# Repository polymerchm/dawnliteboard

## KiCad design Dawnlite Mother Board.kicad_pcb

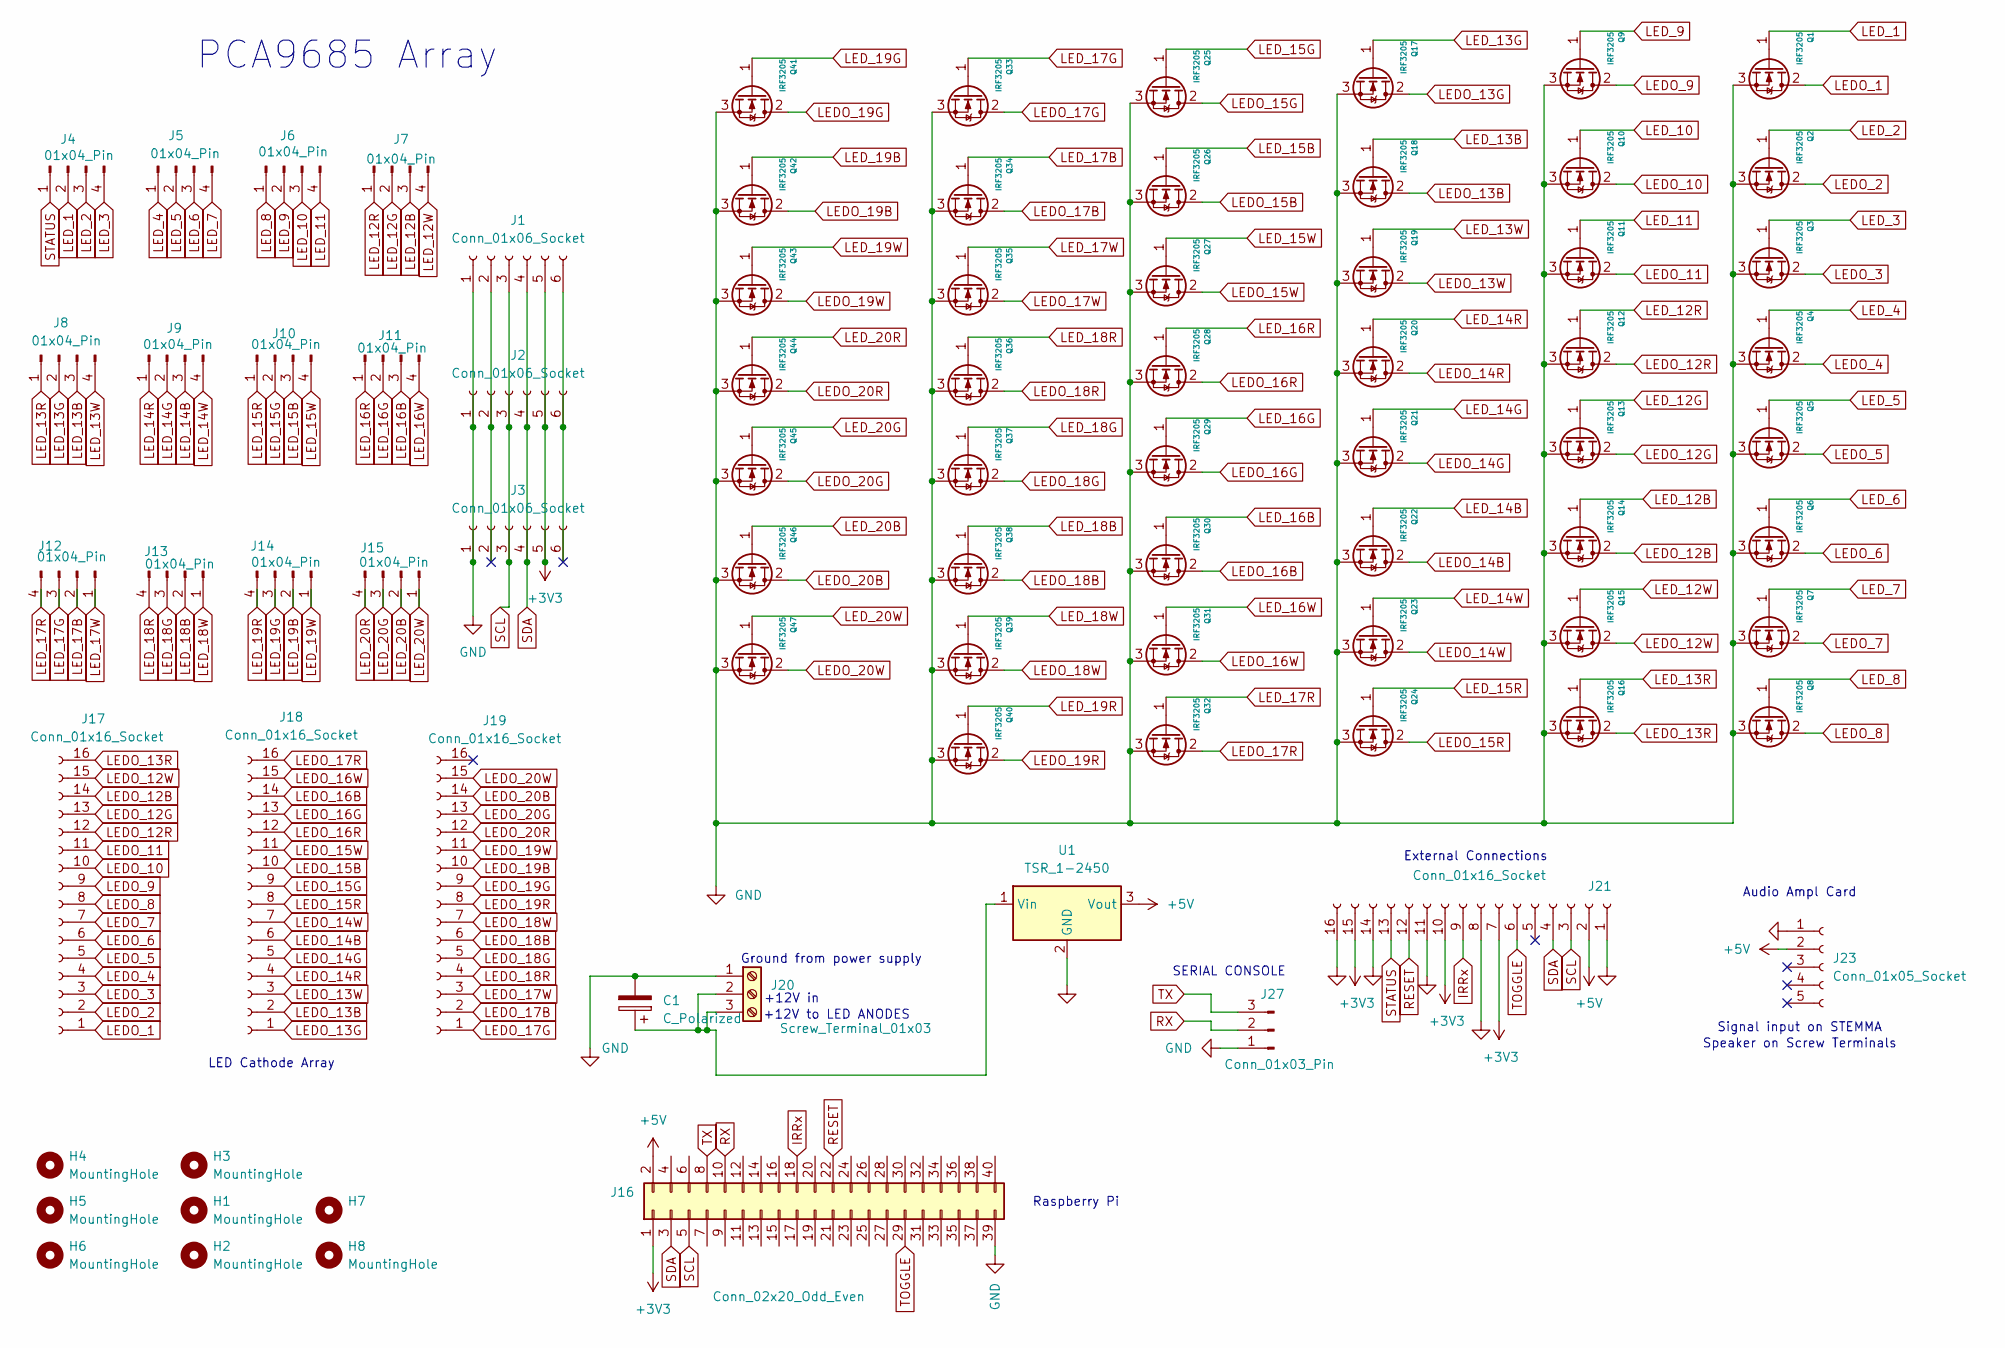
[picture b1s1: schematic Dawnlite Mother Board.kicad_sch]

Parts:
C1: C_Polarized; CP_Radial_D16.0mm_P7.50mm
H1, H2, H3, H4, H5, H6, H7, H8: MountingHole; MountingHole_2.5mm
J1, J2, J3: Conn_01x06_Socket; PinSocket_1x06_P2.54mm_Vertical
J4, J5, J6, J7, J8, J9, J10, J11, J12, J13, J14, J15: 01x04_Pin; PinHeader_1x04_P2.54mm_Vertical
J16: Conn_02x20_Odd_Even; IDC-Header_2x20_P2.54mm_Vertical
J17, J18, J19, J21: Conn_01x16_Socket; PhoenixContact 1985108
J20: Screw_Terminal_01x03; TerminalBlock_Phoenix_MKDS-1,5-3_1x03_P5.00mm_Horizontal
J23: Conn_01x05_Socket; PinHeader_1x04_P2.54mm_Vertical
J27: Conn_01x03_Pin; PinHeader_1x03_P2.54mm_Vertical
Q1, Q2, Q3, Q4, Q5, Q6, Q7, Q8, Q9, Q10, Q11, Q12, Q13, Q14, Q15, Q16, Q17, Q18, Q19, Q20, Q21, Q22, Q23, Q24, Q25, Q26, Q27, Q28, Q29, Q30, Q31, Q32, Q33, Q34, Q35, Q36, Q37, Q38, Q39, Q40, Q41, Q42, Q43, Q44, Q45, Q46, Q47: IRF3205; TO-220-3_Vertical
U1: TSR_1-2450; Converter_DCDC_TRACO_TSR-1_THT

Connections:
+3V3: J1.5, J2.5, J3.5, J16.1, J21.7, J21.10, J21.15
+5V: J16.2, J21.2, J23.2, U1.3 (Vout)
GND: C1.2, J1.1, J2.1, J3.1, J16.39, J20.1, J21.1, J21.8, J21.11, J21.14, J21.16, J23.1, J27.1, Q1.3 (S), Q2.3 (S), Q3.3 (S), Q4.3 (S), Q5.3 (S), Q6.3 (S), Q7.3 (S), Q8.3 (S), Q9.3 (S), Q10.3 (S), Q11.3 (S), Q12.3 (S), Q13.3 (S), Q14.3 (S), Q15.3 (S), Q16.3 (S), Q17.3 (S), Q18.3 (S), Q19.3 (S), Q20.3 (S), Q21.3 (S), Q22.3 (S), Q23.3 (S), Q24.3 (S), Q25.3 (S), Q26.3 (S), Q27.3 (S), Q28.3 (S), Q29.3 (S), Q30.3 (S), Q31.3 (S), Q32.3 (S), Q33.3 (S), Q34.3 (S), Q35.3 (S), Q36.3 (S), Q37.3 (S), Q38.3 (S), Q39.3 (S), Q40.3 (S), Q41.3 (S), Q42.3 (S), Q43.3 (S), Q44.3 (S), Q45.3 (S), Q46.3 (S), Q47.3 (S), U1.2 (GND)
IRRx: J16.18, J21.9
LEDO_1: J17.1, Q1.2 (D)
LEDO_2: J17.2, Q2.2 (D)
LEDO_3: J17.3, Q3.2 (D)
LEDO_4: J17.4, Q4.2 (D)
LEDO_5: J17.5, Q5.2 (D)
LEDO_6: J17.6, Q6.2 (D)
LEDO_7: J17.7, Q7.2 (D)
LEDO_8: J17.8, Q8.2 (D)
LEDO_9: J17.9, Q9.2 (D)
LEDO_10: J17.10, Q10.2 (D)
LEDO_11: J17.11, Q11.2 (D)
LEDO_12B: J17.14, Q14.2 (D)
LEDO_12G: J17.13, Q13.2 (D)
LEDO_12R: J17.12, Q12.2 (D)
LEDO_12W: J17.15, Q15.2 (D)
LEDO_13B: J18.2, Q18.2 (D)
LEDO_13G: J18.1, Q17.2 (D)
LEDO_13R: J17.16, Q16.2 (D)
LEDO_13W: J18.3, Q19.2 (D)
LEDO_14B: J18.6, Q22.2 (D)
LEDO_14G: J18.5, Q21.2 (D)
LEDO_14R: J18.4, Q20.2 (D)
LEDO_14W: J18.7, Q23.2 (D)
LEDO_15B: J18.10, Q26.2 (D)
LEDO_15G: J18.9, Q25.2 (D)
LEDO_15R: J18.8, Q24.2 (D)
LEDO_15W: J18.11, Q27.2 (D)
LEDO_16B: J18.14, Q30.2 (D)
LEDO_16G: J18.13, Q29.2 (D)
LEDO_16R: J18.12, Q28.2 (D)
LEDO_16W: J18.15, Q31.2 (D)
LEDO_17B: J19.2, Q34.2 (D)
LEDO_17G: J19.1, Q33.2 (D)
LEDO_17R: J18.16, Q32.2 (D)
LEDO_17W: J19.3, Q35.2 (D)
LEDO_18B: J19.6, Q38.2 (D)
LEDO_18G: J19.5, Q37.2 (D)
LEDO_18R: J19.4, Q36.2 (D)
LEDO_18W: J19.7, Q39.2 (D)
LEDO_19B: J19.10, Q42.2 (D)
LEDO_19G: J19.9, Q41.2 (D)
LEDO_19R: J19.8, Q40.2 (D)
LEDO_19W: J19.11, Q43.2 (D)
LEDO_20B: J19.14, Q46.2 (D)
LEDO_20G: J19.13, Q45.2 (D)
LEDO_20R: J19.12, Q44.2 (D)
LEDO_20W: J19.15, Q47.2 (D)
LED_1: J4.2, Q1.1 (G)
LED_2: J4.3, Q2.1 (G)
LED_3: J4.4, Q3.1 (G)
LED_4: J5.1, Q4.1 (G)
LED_5: J5.2, Q5.1 (G)
LED_6: J5.3, Q6.1 (G)
LED_7: J5.4, Q7.1 (G)
LED_8: J6.1, Q8.1 (G)
LED_9: J6.2, Q9.1 (G)
LED_10: J6.3, Q10.1 (G)
LED_11: J6.4, Q11.1 (G)
LED_12B: J7.3, Q14.1 (G)
LED_12G: J7.2, Q13.1 (G)
LED_12R: J7.1, Q12.1 (G)
LED_12W: J7.4, Q15.1 (G)
LED_13B: J8.3, Q18.1 (G)
LED_13G: J8.2, Q17.1 (G)
LED_13R: J8.1, Q16.1 (G)
LED_13W: J8.4, Q19.1 (G)
LED_14B: J9.3, Q22.1 (G)
LED_14G: J9.2, Q21.1 (G)
LED_14R: J9.1, Q20.1 (G)
LED_14W: J9.4, Q23.1 (G)
LED_15B: J10.3, Q26.1 (G)
LED_15G: J10.2, Q25.1 (G)
LED_15R: J10.1, Q24.1 (G)
LED_15W: J10.4, Q27.1 (G)
LED_16B: J11.3, Q30.1 (G)
LED_16G: J11.2, Q29.1 (G)
LED_16R: J11.1, Q28.1 (G)
LED_16W: J11.4, Q31.1 (G)
LED_17B: J12.2, Q34.1 (G)
LED_17G: J12.3, Q33.1 (G)
LED_17R: J12.4, Q32.1 (G)
LED_17W: J12.1, Q35.1 (G)
LED_18B: J13.2, Q38.1 (G)
LED_18G: J13.3, Q37.1 (G)
LED_18R: J13.4, Q36.1 (G)
LED_18W: J13.1, Q39.1 (G)
LED_19B: J14.2, Q42.1 (G)
LED_19G: J14.3, Q41.1 (G)
LED_19R: J14.4, Q40.1 (G)
LED_19W: J14.1, Q43.1 (G)
LED_20B: J15.2, Q46.1 (G)
LED_20G: J15.3, Q45.1 (G)
LED_20R: J15.4, Q44.1 (G)
LED_20W: J15.1, Q47.1 (G)
unnamed: C1.1, J20.2, J20.3, U1.1 (Vin)
RESET: J16.22, J21.12
RX: J16.10, J27.2
SCL: J1.3, J2.3, J3.3, J16.5, J21.3
SDA: J1.4, J2.4, J3.4, J16.3, J21.4
STATUS: J4.1, J21.13
TOGGLE: J16.29, J21.6
TX: J16.8, J27.3

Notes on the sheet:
Ground from power supply
+12V in
Signal input on STEMMA
+12V to LED ANODES
PCA9685 Array
External Connections
Audio Ampl Card
Speaker on Screw Terminals
SERIAL CONSOLE
LED Cathode Array
Raspberry Pi

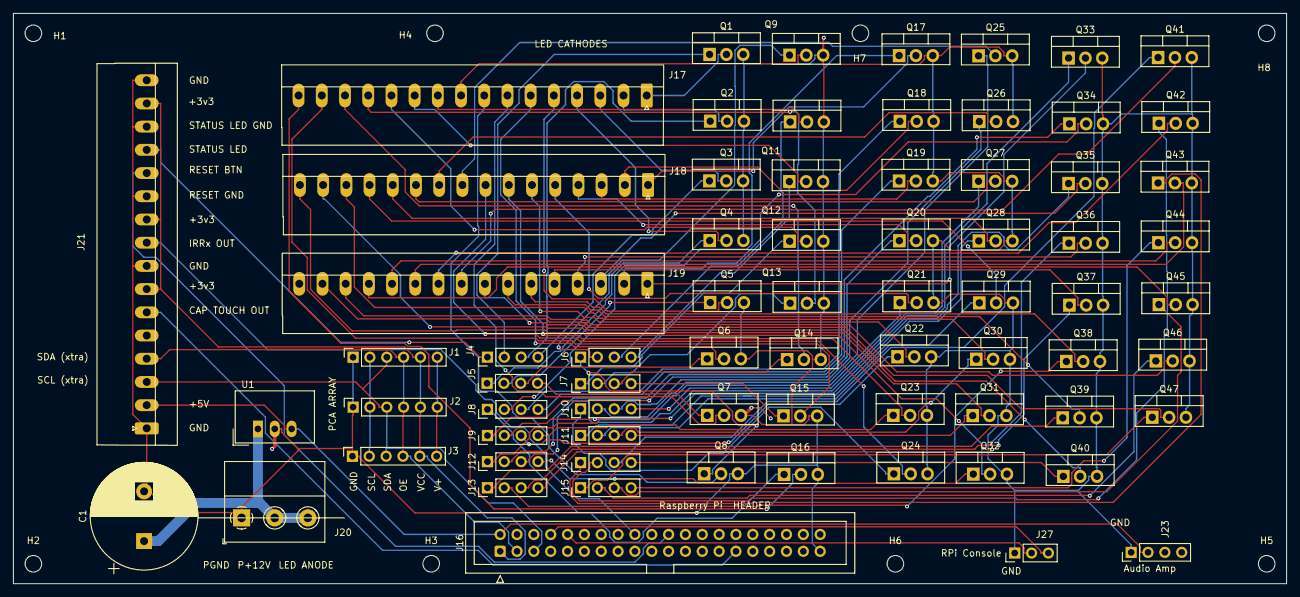
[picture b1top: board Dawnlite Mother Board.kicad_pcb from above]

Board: 2 copper layers, 192.0 x 86.0 mm, 80 parts (0 on the bottom side), 106 nets.

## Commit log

2024-05-10 updated ignore removed zips
2024-05-11 remote duplicates
